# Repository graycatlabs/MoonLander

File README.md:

# MoonLander

A small, low cost and low power Cortex-M0+ dev board based on the LPC824.

## License

The schematics and PCB design files are licensed under the Creative Commons Attribution-ShareAlike 3.0 license (https://creativecommons.org/licenses/by-sa/3.0/us/).

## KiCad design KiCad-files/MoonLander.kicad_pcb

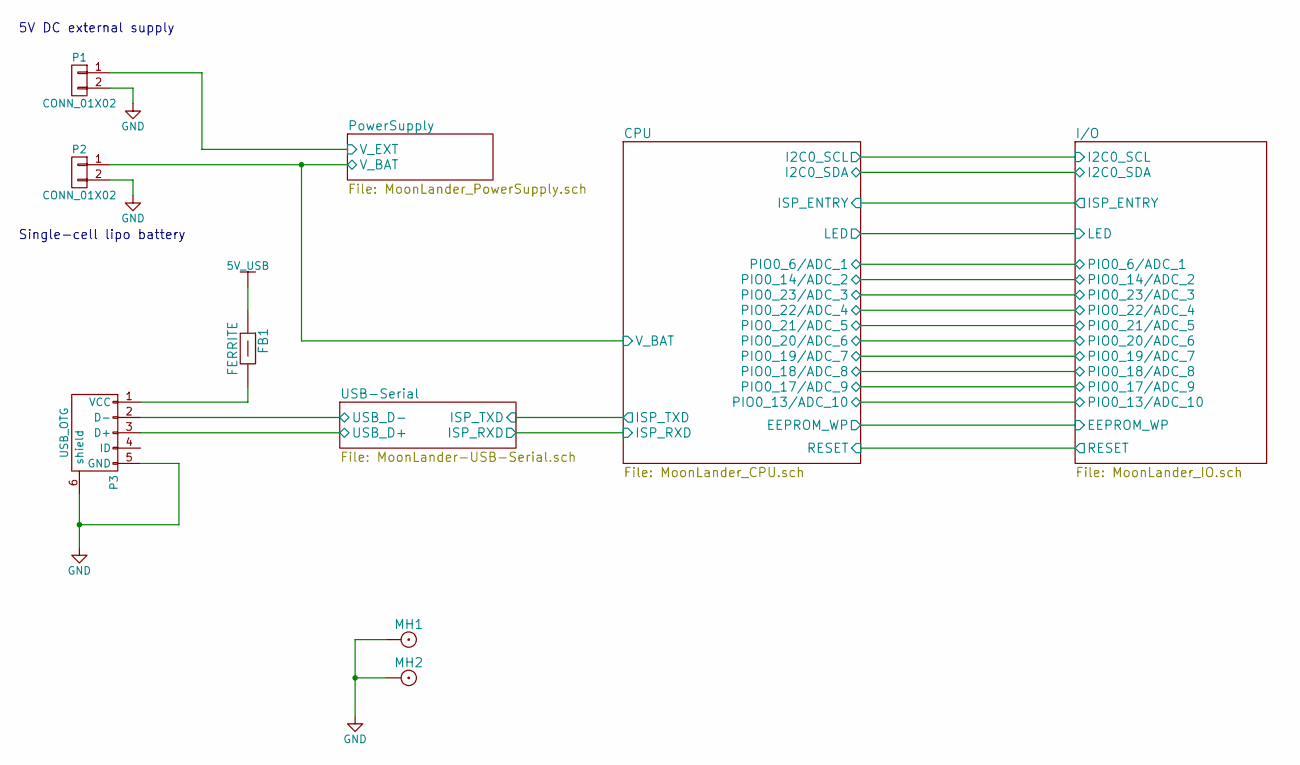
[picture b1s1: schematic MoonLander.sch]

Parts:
FB1: FERRITE; R_0402
MH1, MH2: MountingHole; MH-M2
P1: CONN_01X02; Socket_Strip_Straight_1x02
P2: CONN_01X02; JST-LIPO-SMT
P3: USB_OTG; USB_Micro-B

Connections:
5V_USB: FB1.1 (A); also elsewhere on the board
/CPU/V_BAT: P2.1; also elsewhere on the board
/PowerSupply/V_EXT: P1.1; also elsewhere on the board
/USB-Serial/USB_D+: P3.3 (D+); also elsewhere on the board
/USB-Serial/USB_D-: P3.2 (D-); also elsewhere on the board
GND: MH1.1, MH2.1, P1.2, P2.2, P3.5 (GND), P3.6 (shield); also elsewhere on the board
unnamed: FB1.2 (B), P3.1 (VCC)

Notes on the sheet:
Single-cell lipo battery
5V DC external supply

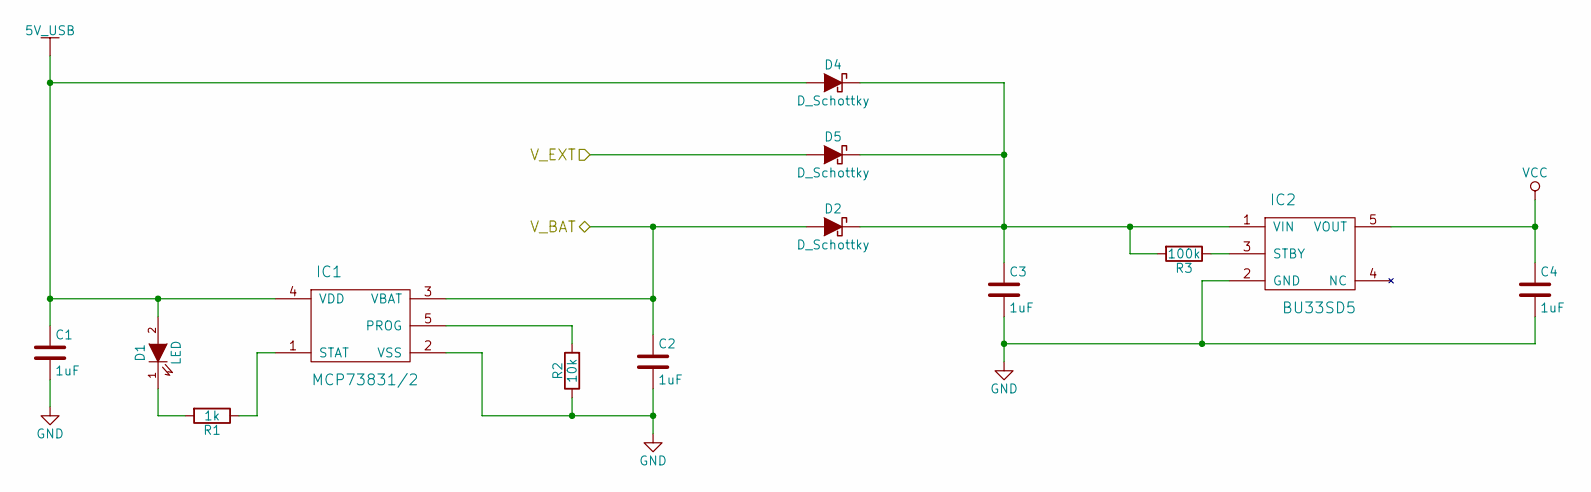
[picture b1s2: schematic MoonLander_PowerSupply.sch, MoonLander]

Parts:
C1, C2, C3, C4: 1uF; C_0402
D1: LED; LED-0603
D2, D4, D5: D_Schottky; SOD-323
IC1: MCP73831/2; SSOP5
IC2: BU33SD5; SSOP5
R1: 1k; R_0402
R2: 10k; R_0402
R3: 100k; R_0402

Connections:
5V_USB: C1.1, D1.2 (A), D4.2 (A), IC1.4 (VDD); also elsewhere on the board
/CPU/V_BAT: C2.1, D2.2 (A), IC1.3 (VBAT); also elsewhere on the board
/PowerSupply/V_EXT: D5.2 (A); also elsewhere on the board
GND: C1.2, C2.2, C3.2, C4.2, IC1.2 (VSS), IC2.2 (GND), R2.1; also elsewhere on the board
unnamed: C3.1, D2.1 (K), D4.1 (K), D5.1 (K), IC2.1 (VIN), R3.2
unnamed: D1.1 (K), R1.2
unnamed: IC1.1 (STAT), R1.1
unnamed: IC1.5 (PROG), R2.2
unnamed: IC2.3 (STBY), R3.1
VCC: C4.1, IC2.5 (VOUT); also elsewhere on the board

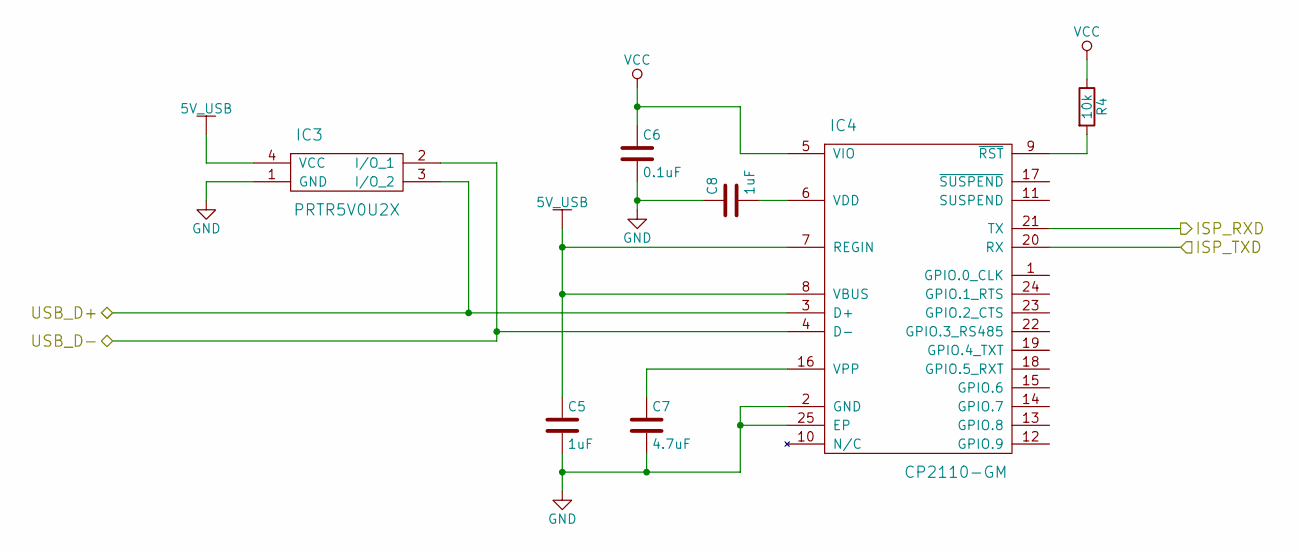
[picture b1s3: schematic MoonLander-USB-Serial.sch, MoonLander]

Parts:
C5, C8: 1uF; C_0402
C6: 0.1uF; C_0402
C7: 4.7uF; C_0402
IC3: PRTR5V0U2X; SOT143B
IC4: CP2110-GM; QFN-24-1EP_4x4mm_Pitch0.5mm
R4: 10k; R_0402

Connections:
5V_USB: C5.1, IC3.4 (VCC), IC4.7 (REGIN), IC4.8 (VBUS); also elsewhere on the board
/CPU/ISP_ENTRY: IC4.13 (GPIO.8); also elsewhere on the board
/CPU/ISP_RST: IC4.12 (GPIO.9); also elsewhere on the board
/CPU/ISP_RXD: IC4.21 (TX); also elsewhere on the board
/CPU/ISP_TXD: IC4.20 (RX); also elsewhere on the board
/USB-Serial/USB_D+: IC3.3 (I/O_2), IC4.3 (D+); also elsewhere on the board
/USB-Serial/USB_D-: IC3.2 (I/O_1), IC4.4 (D-); also elsewhere on the board
GND: C5.2, C6.2, C7.2, C8.1, IC3.1 (GND), IC4.2 (GND), IC4.25 (EP); also elsewhere on the board
unnamed: C7.1, IC4.16 (VPP)
unnamed: C8.2, IC4.6 (VDD)
unnamed: IC4.9 (~RST), R4.2
VCC: C6.1, IC4.5 (VIO), R4.1; also elsewhere on the board

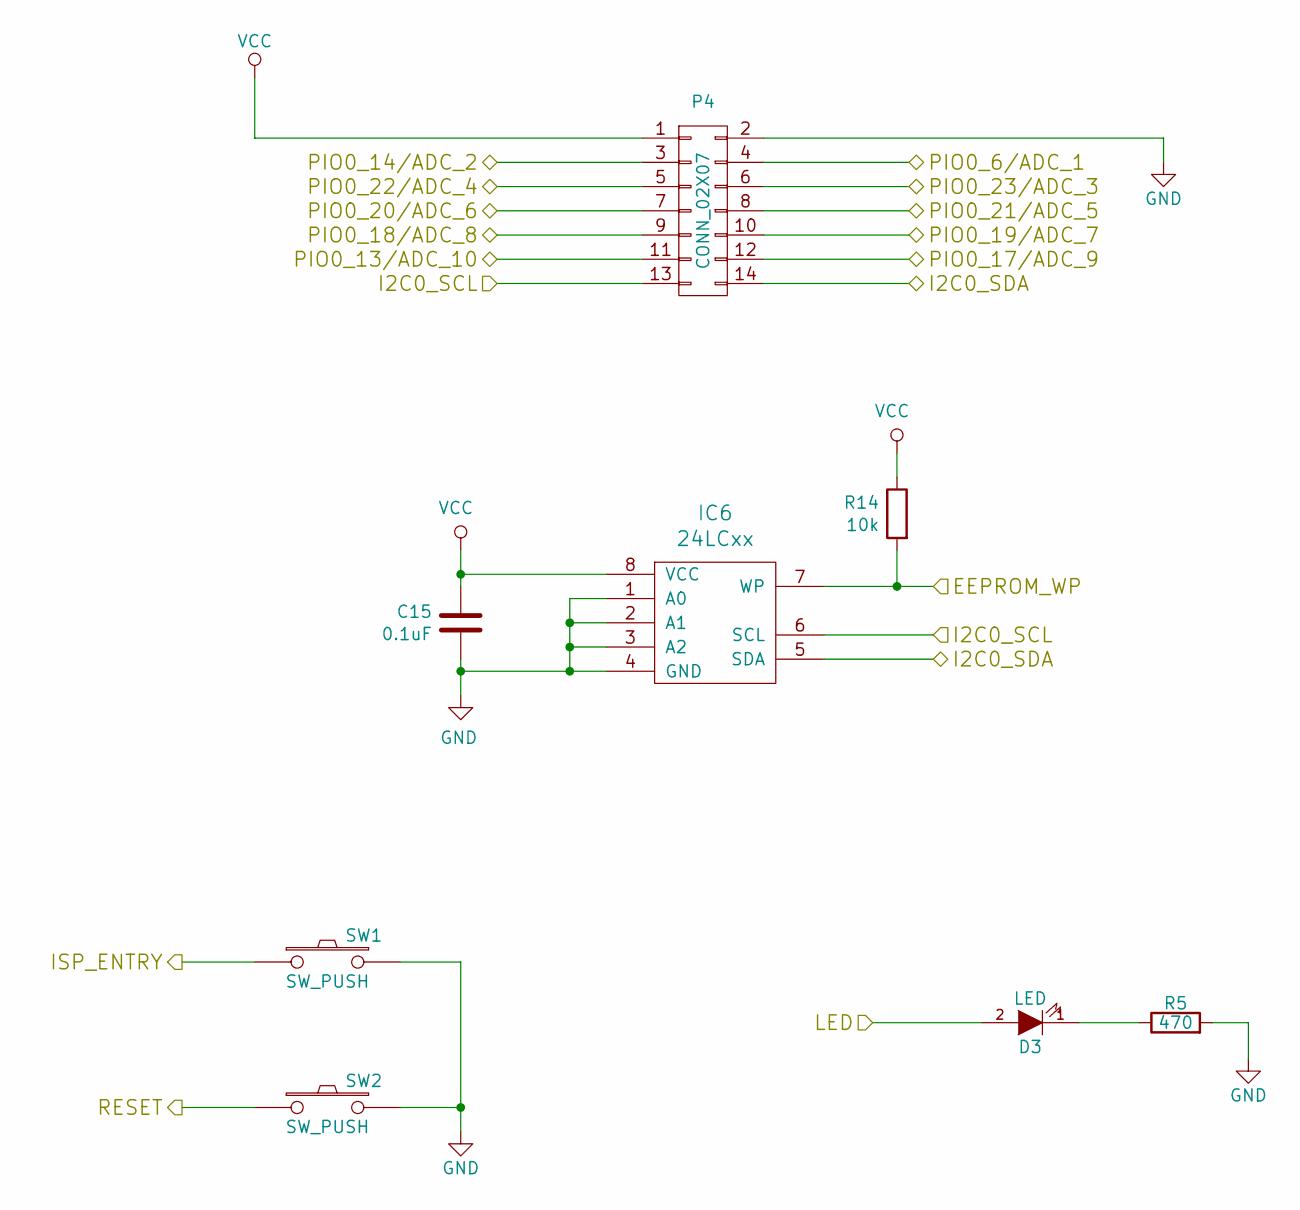
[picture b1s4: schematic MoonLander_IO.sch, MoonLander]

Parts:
C15: 0.1uF; C_0402
D3: LED; LED-0603
IC6: 24LCxx; DFN-8-1EP_2x2mm_Pitch0.5mm
P4: CONN_02X07; Header_2mm_2x7
R5: 470; R_0402
R14: 10k; R_0402
SW1, SW2: SW_PUSH; PTS810

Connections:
/CPU/EEPROM_WP: IC6.7 (WP), R14.2; also elsewhere on the board
/CPU/I2C0_SCL: IC6.6 (SCL), P4.13; also elsewhere on the board
/CPU/I2C0_SDA: IC6.5 (SDA), P4.14; also elsewhere on the board
/CPU/LED: D3.2 (A); also elsewhere on the board
/CPU/PIO0_6/ADC_1: P4.4; also elsewhere on the board
/CPU/PIO0_13/ADC_10: P4.11; also elsewhere on the board
/CPU/PIO0_14/ADC_2: P4.3; also elsewhere on the board
/CPU/PIO0_17/ADC_9: P4.12; also elsewhere on the board
/CPU/PIO0_18/ADC_8: P4.9; also elsewhere on the board
/CPU/PIO0_19/ADC_7: P4.10; also elsewhere on the board
/CPU/PIO0_20/ADC_6: P4.7; also elsewhere on the board
/CPU/PIO0_21/ADC_5: P4.8; also elsewhere on the board
/CPU/PIO0_22/ADC_4: P4.5; also elsewhere on the board
/CPU/PIO0_23/ADC_3: P4.6; also elsewhere on the board
/CPU/RESET: SW2.1; also elsewhere on the board
/CPU/SW1: SW1.1; also elsewhere on the board
GND: C15.2, IC6.1 (A0), IC6.2 (A1), IC6.3 (A2), IC6.4 (GND), P4.2, R5.2, SW1.2, SW2.2; also elsewhere on the board
unnamed: D3.1 (K), R5.1
VCC: C15.1, IC6.8 (VCC), P4.1, R14.1; also elsewhere on the board

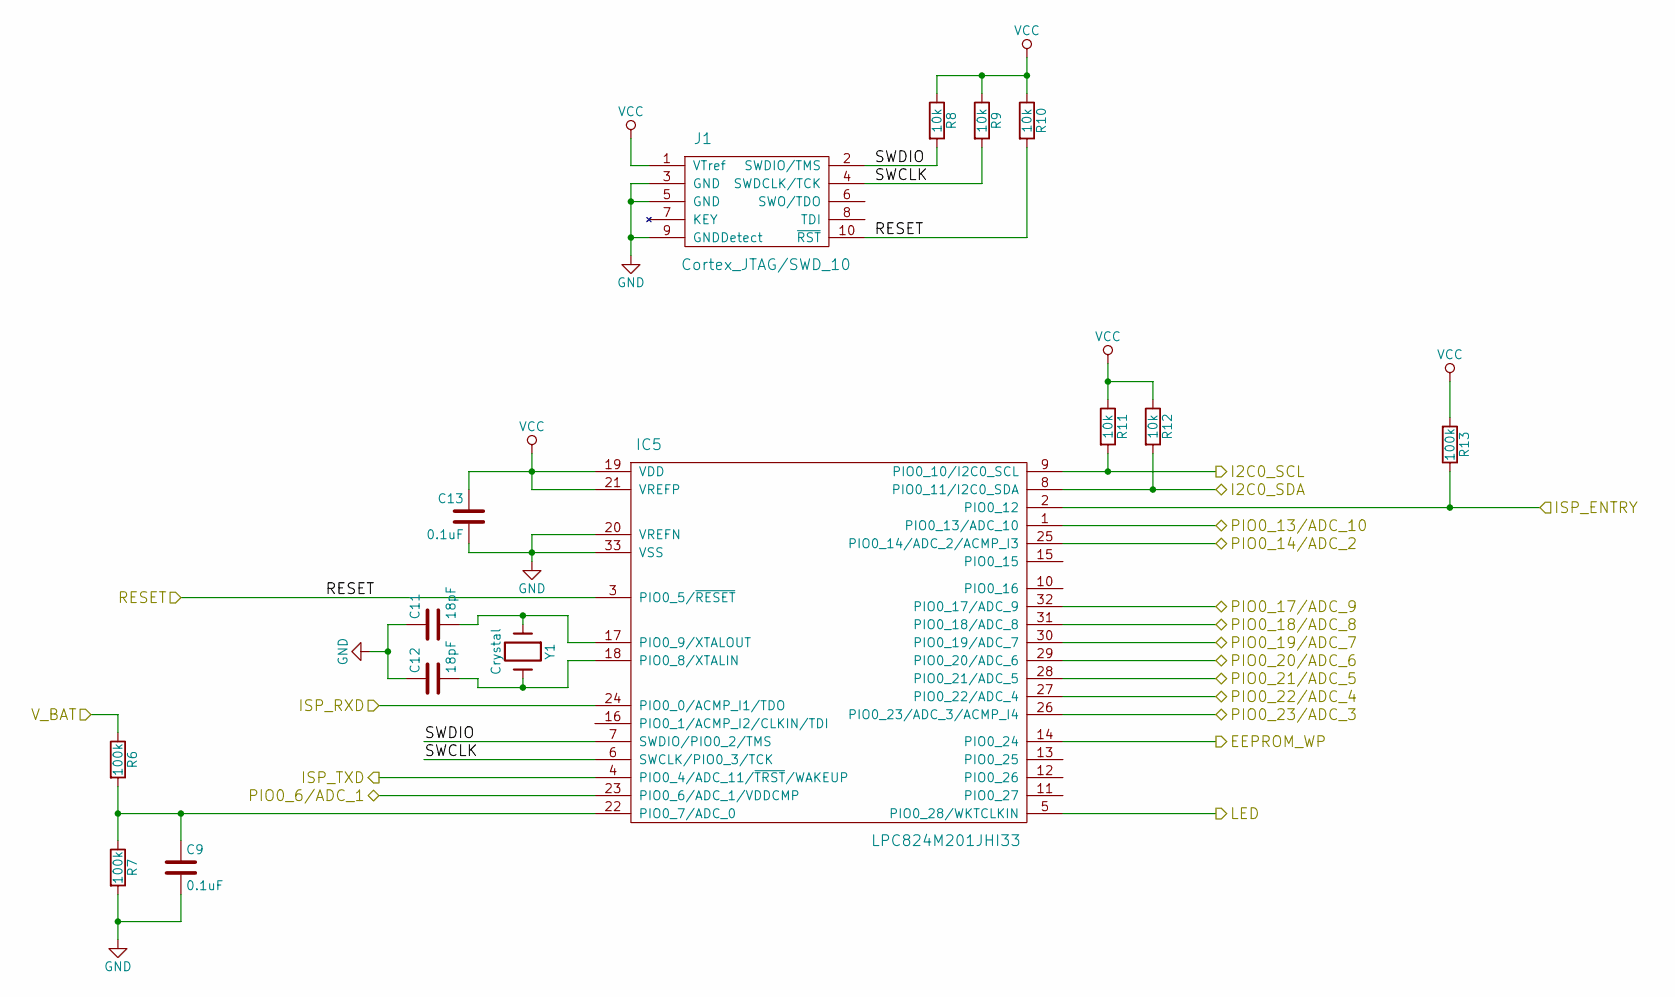
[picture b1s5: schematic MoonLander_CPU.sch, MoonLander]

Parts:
C9, C13: 0.1uF; C_0402
C11, C12: 18pF; C_0402
IC5: LPC824M201JHI33; QFN-32-1EP_5x5mm_Pitch0.5mm
J1: Cortex_JTAG/SWD_10; Pin_Header_Straight_2x05_Pitch1.27mm
R6, R7, R13: 100k; R_0402
R8, R9, R10, R11, R12: 10k; R_0402
Y1: Crystal; crystal_FA238-TSX3225

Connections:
/CPU/EEPROM_WP: IC5.14 (PIO0_24); also elsewhere on the board
/CPU/I2C0_SCL: IC5.9 (PIO0_10/I2C0_SCL), R11.2; also elsewhere on the board
/CPU/I2C0_SDA: IC5.8 (PIO0_11/I2C0_SDA), R12.2; also elsewhere on the board
/CPU/ISP_RXD: IC5.24 (PIO0_0/ACMP_I1/TDO); also elsewhere on the board
/CPU/ISP_TXD: IC5.4 (PIO0_4/ADC_11/~TRST~/WAKEUP); also elsewhere on the board
/CPU/LED: IC5.5 (PIO0_28/WKTCLKIN); also elsewhere on the board
/CPU/PIO0_6/ADC_1: IC5.23 (PIO0_6/ADC_1/VDDCMP); also elsewhere on the board
/CPU/PIO0_13/ADC_10: IC5.1 (PIO0_13/ADC_10); also elsewhere on the board
/CPU/PIO0_14/ADC_2: IC5.25 (PIO0_14/ADC_2/ACMP_I3); also elsewhere on the board
/CPU/PIO0_17/ADC_9: IC5.32 (PIO0_17/ADC_9); also elsewhere on the board
/CPU/PIO0_18/ADC_8: IC5.31 (PIO0_18/ADC_8); also elsewhere on the board
/CPU/PIO0_19/ADC_7: IC5.30 (PIO0_19/ADC_7); also elsewhere on the board
/CPU/PIO0_20/ADC_6: IC5.29 (PIO0_20/ADC_6); also elsewhere on the board
/CPU/PIO0_21/ADC_5: IC5.28 (PIO0_21/ADC_5); also elsewhere on the board
/CPU/PIO0_22/ADC_4: IC5.27 (PIO0_22/ADC_4); also elsewhere on the board
/CPU/PIO0_23/ADC_3: IC5.26 (PIO0_23/ADC_3/ACMP_I4); also elsewhere on the board
/CPU/RESET: IC5.3 (PIO0_5/~RESET), J1.10 (~RST), R10.2; also elsewhere on the board
/CPU/SW1: IC5.10 (PIO0_16); also elsewhere on the board
/CPU/SWCLK: IC5.6 (SWCLK/PIO0_3/TCK), J1.4 (SWDCLK/TCK), R9.2
/CPU/SWDIO: IC5.7 (SWDIO/PIO0_2/TMS), J1.2 (SWDIO/TMS), R8.2
/CPU/V_BAT: R6.1; also elsewhere on the board
GND: C9.2, C11.1, C12.1, C13.2, IC5.20 (VREFN), IC5.33 (VSS), J1.3 (GND), J1.5 (GND), J1.9 (GNDDetect), R7.2; also elsewhere on the board
unnamed: C9.1, IC5.22 (PIO0_7/ADC_0), R6.2, R7.1
unnamed: C11.2, IC5.17 (PIO0_9/XTALOUT), Y1.1
unnamed: C12.2, IC5.18 (PIO0_8/XTALIN), Y1.2
unnamed 53: IC5.2 (PIO0_12), R13.1; also elsewhere on the board
VCC: C13.1, IC5.19 (VDD), IC5.21 (VREFP), J1.1 (VTref), R8.1, R9.1, R10.1, R11.1, R12.1, R13.2; also elsewhere on the board

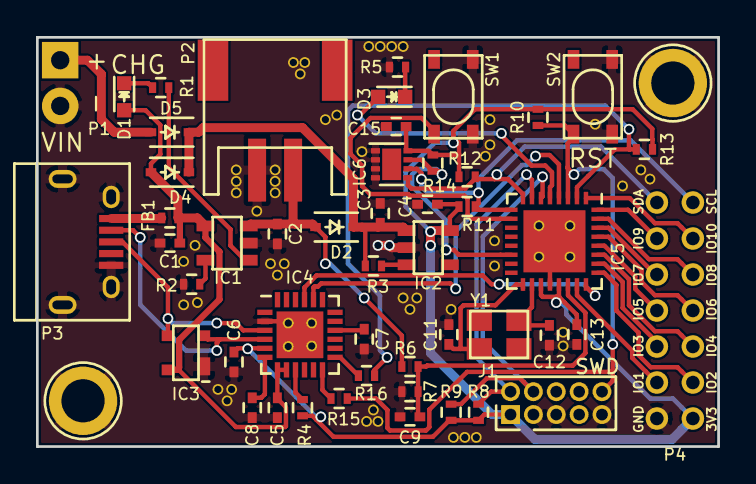
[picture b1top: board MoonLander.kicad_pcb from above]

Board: 2 copper layers, 37.8 x 22.7 mm, 51 parts (0 on the bottom side), 43 nets.

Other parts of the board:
R15, R16: 100; R_0402

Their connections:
/CPU/ISP_ENTRY: R16.1; also elsewhere on the board
/CPU/ISP_RST: R15.2; also elsewhere on the board
/CPU/RESET: R15.1; also elsewhere on the board
unnamed 53: R16.2; also elsewhere on the board

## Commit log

2015-12-03 first commit - schematic design partially done
2015-12-03 schematic nearing prototype - time for some layout
2015-12-06 first whack at layout - unrouted
2015-12-06 moved some things around
2015-12-06 routing complete
2015-12-06 moved header to connect fills below
2015-12-06 checking CircuitHub cost with 2 layers
2015-12-06 simplified 2 layer version
2015-12-07 need to squeeze on some mounting holes...
2015-12-07 made room for two M2 mounting holes
2015-12-07 added some dimensions
2015-12-07 moved a few things
2015-12-07 switched microUSB footprint
2015-12-07 fixed usb ref des
2015-12-07 generated gerbers
2015-12-21 fixed reversed USB pinout
2015-12-24 fixed switch footprint and pinout
2016-01-09 bypass battery if USB connected
2016-01-09 switched microUSB footprint, rerouted with new schottkys
2016-01-09 use STITCH_VIA footprint for via stitching
2016-01-12 added some silk
2016-01-13 remove 3d model from VIN connector
2016-01-13 added title, license
2016-01-13 organizing
2016-01-13 generated PDF schematics
2016-01-13 a README
2016-01-14 added submodule for cp2110 library
2016-01-14 added CoC
2016-01-20 added I2C EEPROM, redid ground stitching
2016-02-05 fixed header symbol/footprint naming, minor changes
2016-02-05 drive ISP_ENTRY and RST from CP2110 GPIO outputs
2016-02-05 moved SWD header a bit
2016-02-05 regenerate gerbers, add paste file
2016-02-05 moved P4 silk label
2016-02-05 zipped Gerbers
2016-02-05 typo
2016-02-05 changed drill file extension to make oshpark happy
2016-05-10 rev. B PDF schematics

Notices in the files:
KiCad-files/MoonLander.kicad_pcb:
CC BY-SA
